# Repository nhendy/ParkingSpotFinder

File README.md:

# ECE477-GarageMonitoringSystem

## Links
- [Initial proposal](https://docs.google.com/document/d/1f3pLotd3W6YBDPHfsqi8Z5CGvJJmyrOUrbO1O-sXBOU/edit)

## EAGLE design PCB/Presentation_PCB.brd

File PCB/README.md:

# Pinout

## MCU to CM3 UART5

| STM Pins      | CM3 Pins   | Functionality   |
| ------------- | ---------- | --------------- |
| PD_2          | 51          | USART5 RX  -->  GPIO14 TX|
| PC_12         | 53          | USART5 TX  -->  GPIO15 RX|
## MCU to JTAG
| STM Pins      | JTAG Pins    | Functionality   |
| ------------- | ----------   | --------------- |
| PA_13         | 1            | SWDIO  -->  VDD|
| PA_14         | 2            | SWCLK  -->  SWDIO|
| PA_15         | 3,5,9        | JTDI  -->  GND|
| PB_3          | 6            | SWO   -->  SWO|
| PB_4          | 10           | JTRST  -->  RST|

## MCU to Sensor UART7
| STM Pins      | Sensor Pins    | Functionality   |
| ------------- | ----------   | --------------- |
| PF_6         | Pin 5            | RX  -->  Serial out|
| PA_7         | _          | |
## MCU to LCD
| STM Pins      | LCD Pins    | Functionality   |
| ------------- | ----------   | --------------- |
| PB_2         | 3            | QUAD_SPI_SCLK  |
| PE_7         | 5            | QUAD_SPI_IO0  |
| PE_8         | 4            | QUAD_SPI_IO1|
| PE_9         | 11           | QUAD_SPI_IO2|
| PE_10         | 12          | QUAD_SPI_IO3|

## MCU to FTDI UART1

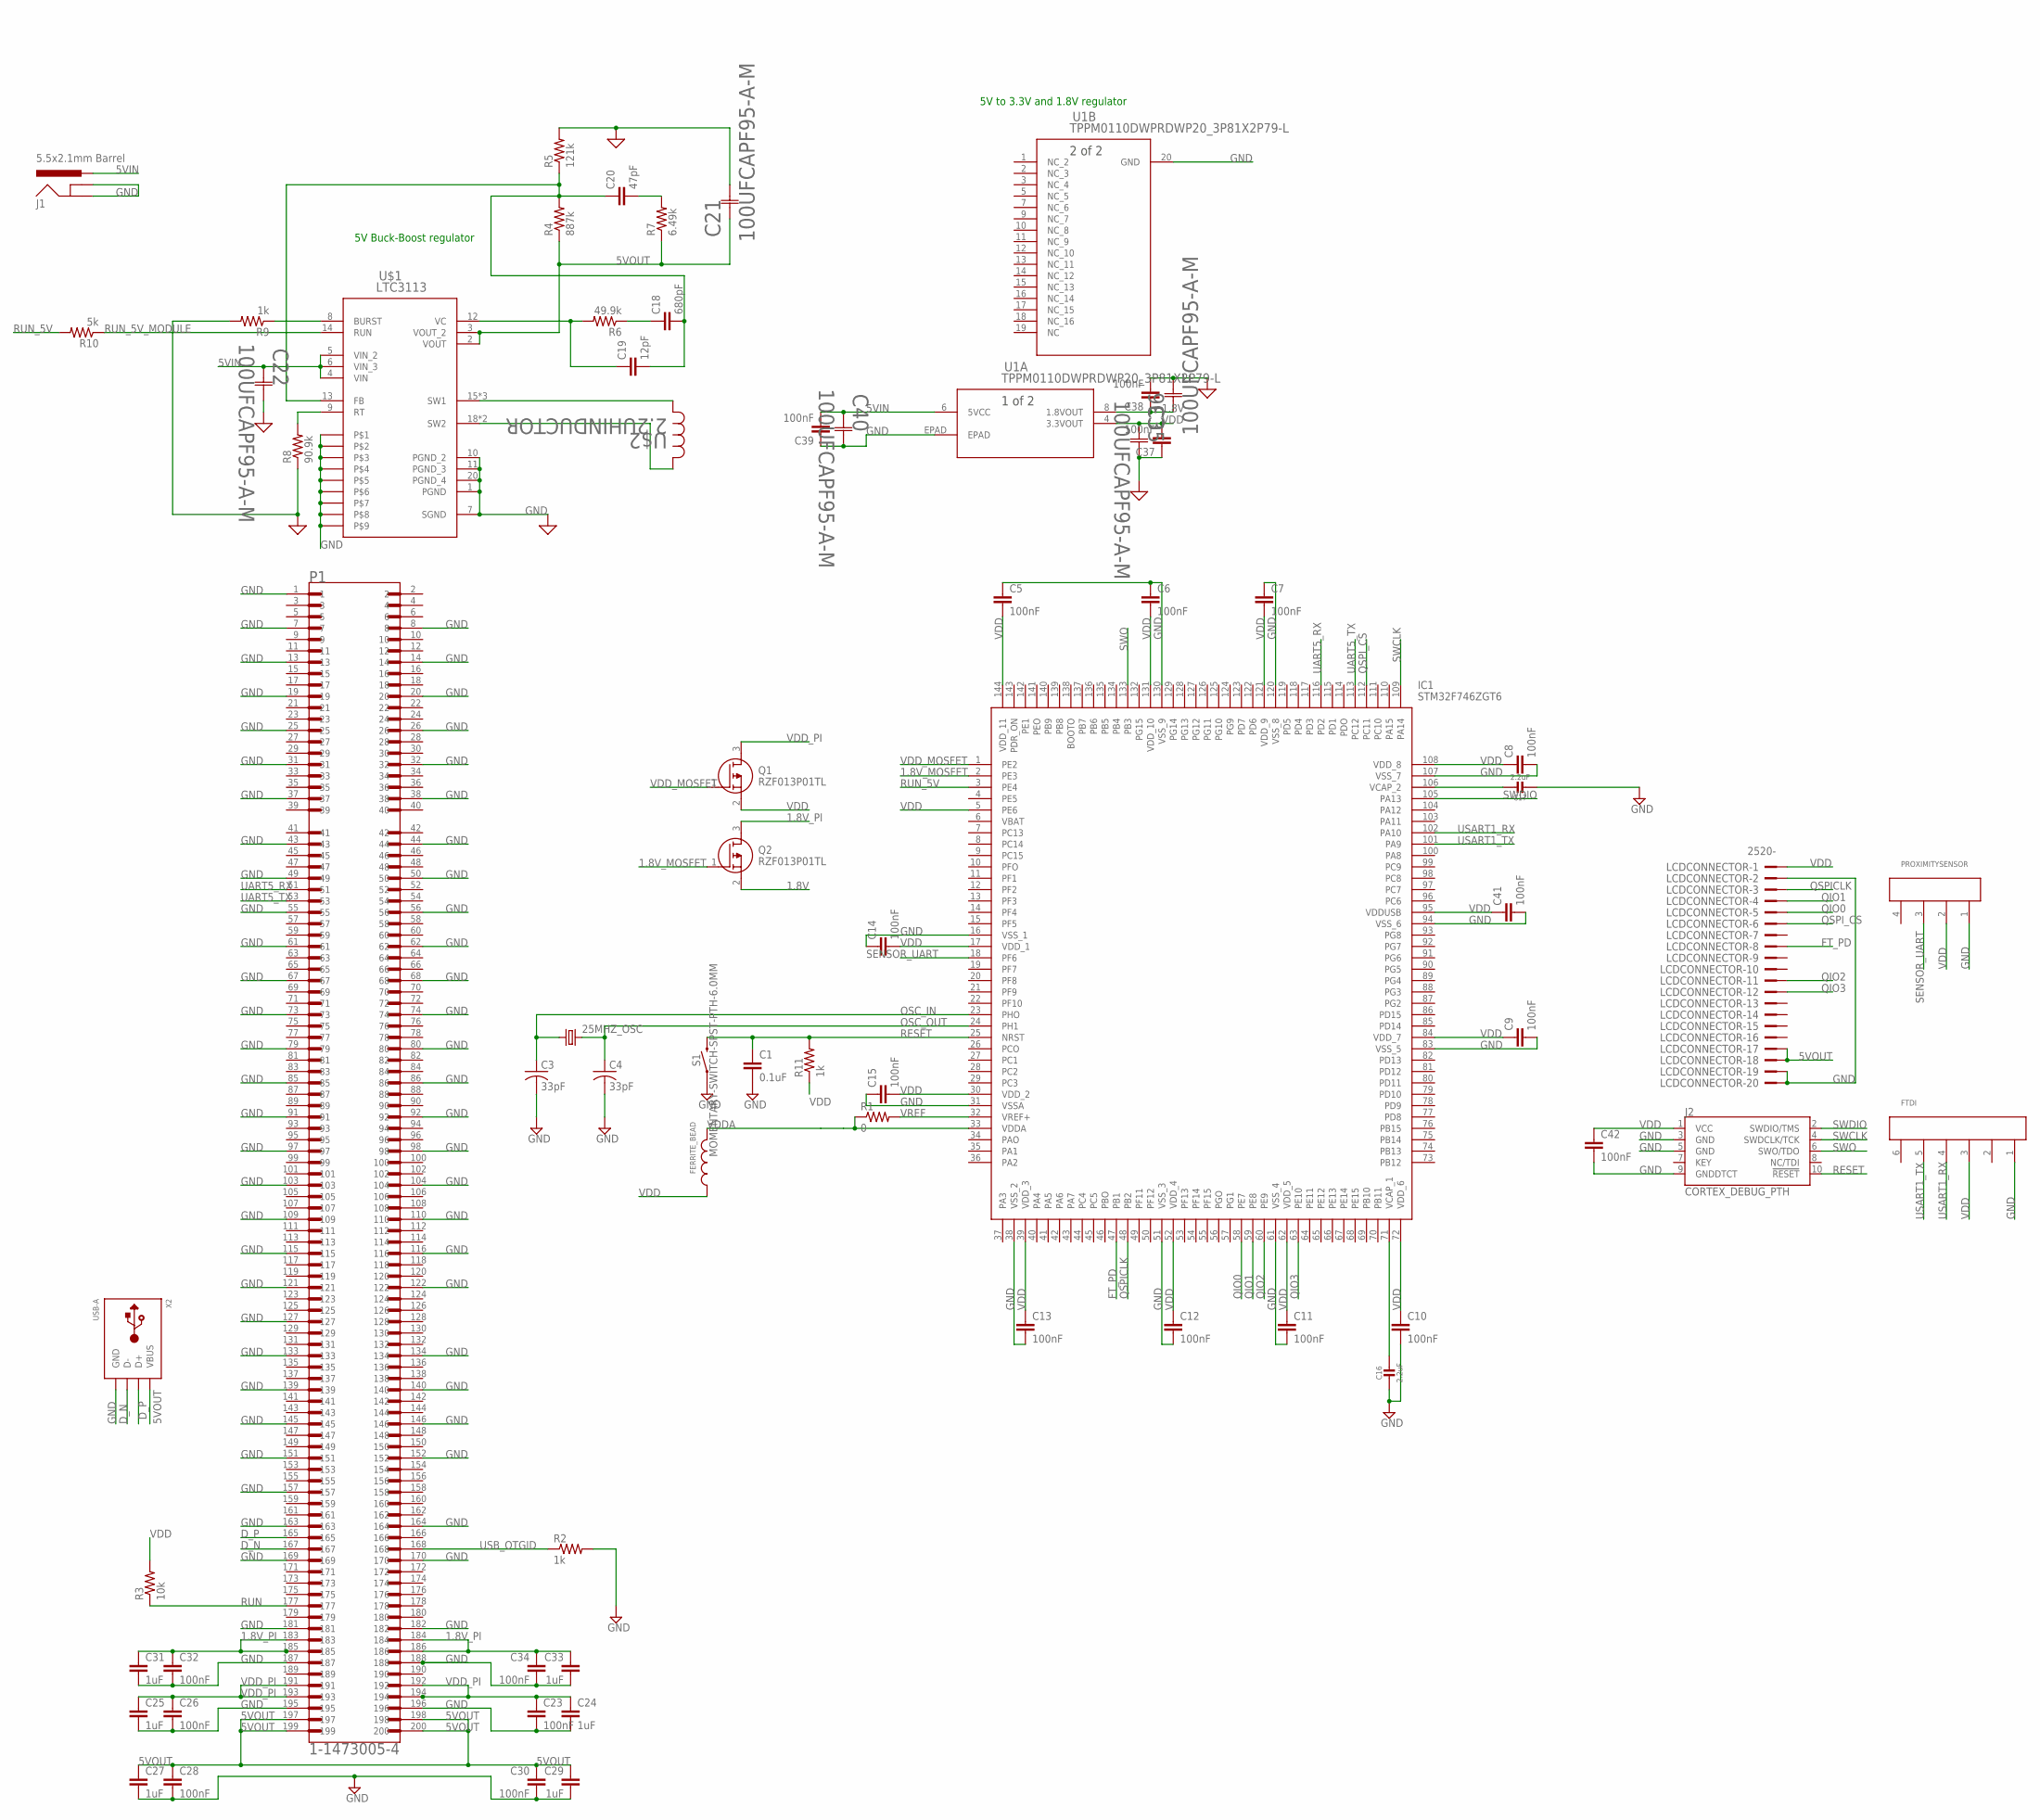
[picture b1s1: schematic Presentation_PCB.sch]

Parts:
25MHZ_OSC: CRYSTALHC49UP; HC49UP
C1: 0.1uF; C0805
C3, C4: 33pF; C0805
C5, C6, C7, C8, C9, C10, C11, C12, C13, C14, C15, C23, C26, C28, C30, C32, C34, C37, C38, C39, C41, C42: 100nF; C0805
C16, C17: 2.2uF; 0805-NO
C18: 680pF; C0805
C19: 12pF; C0805
C20: 47pF; C0805
C21, C22, C35, C36, C40: 100UFCAPF95-A-M; F95-A-M
C24, C25, C27, C29, C31, C33: 1uF; C0805
FERRITE_BEAD: WE-CBA_0805_782853112_HC; WE-CBA_0805(W=4)
FTDI: 66100611622
IC1: STM32F746ZGT6; QFP50P2200X2200X160-144N
J1: 5.5x2.1mm Barrel; POWER_JACK_SMD
J2: CORTEX_DEBUG_PTH; 2X5-PTH-1.27MM
LCDCONNECTOR: 2520-; PAK100/2500-20
P1: 1-1473005-4; TE_1-1473005-4
PROXIMITYSENSOR: 66100411622
Q1, Q2: RZF013P01TL; SOT65P210X85-3N
R1: 0; R0805
R2, R9, R11: 1k; R0805
R3: 10k; R0805
R4: 887k; R0805
R5: 121k; R0805
R6: 49.9k; R0805
R7: 6.49k; R0805
R8: 90.9k; R0805
R10: 5k; R0805
S1: MOMENTARY-SWITCH-SPST-PTH-6.0MM; TACTILE_SWITCH_PTH_6.0MM
U1: TPPM0110DWPRDWP20_3P81X2P79-L; DWP20_3P81X2P79-L
U$1: LTC3113; TSSOP-20_FE/CA
U$2: 2.2UHINDUCTOR; IND_10040
X2: USB-A; MOLEX_480371000

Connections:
1.8V: C36.1, C38.1, Q2.2 (S), U1.8 (1.8VOUT)
1.8V_MOSFET: IC1.2 (PE3), Q2.1 (G)
1.8V_PI: C31.1, C32.1, C33.1, C34.1, P1.183, P1.184, P1.185, P1.186, Q2.3 (D)
5VIN: C22.1, C39.2, C40.1, J1.VIN0 (PWR), U1.6 (5VCC), U$1.4 (VIN), U$1.5 (VIN_2), U$1.6 (VIN_3)
5VOUT: C21.1, C27.1, C28.1, C29.1, C30.1, LCDCONNECTOR.17, LCDCONNECTOR.18, P1.197, P1.198, P1.199, P1.200, R4.1, R7.1, U$1.2 (VOUT), U$1.3 (VOUT_2), X2.1 (VBUS)
D_N: P1.167, X2.2 (D-)
D_P: P1.165, X2.3 (D+)
FT_PD: IC1.47 (PB1), LCDCONNECTOR.8
GND: C1.2, C3.2, C4.2, C5.1, C6.1, C7.1, C8.2, C9.2, C10.2, C11.2, C12.2, C13.2, C14.1, C15.1, C16.2, C17.2, C21.2, C22.2, C23.2, C24.2, C25.2, C26.2, C27.2, C28.2, C29.2, C30.2, C31.2, C32.2, C33.2, C34.2, C35.2, C36.2, C37.1, C38.2, C39.1, C40.2, C41.2, C42.2, FTDI.1, IC1.16 (VSS_1), IC1.31 (VSSA), IC1.38 (VSS_2), IC1.51 (VSS_3), IC1.61 (VSS_4), IC1.83 (VSS_5), IC1.94 (VSS_6), IC1.107 (VSS_7), IC1.120 (VSS_8), IC1.130 (VSS_9), J1.GND (GNDBREAK), J1.P$4 (GND), J2.3 (GND), J2.5 (GND), J2.9 (GNDDTCT), LCDCONNECTOR.2, LCDCONNECTOR.19, LCDCONNECTOR.20, P1.1, P1.7, P1.8, P1.13, P1.14, P1.19, P1.20, P1.25, P1.26, P1.31, P1.32, P1.37, P1.38, P1.43, P1.44, P1.49, P1.50, P1.55, P1.56, P1.61, P1.62, P1.67, P1.68, P1.73, P1.74, P1.79, P1.80, P1.85, P1.86, P1.91, P1.92, P1.97, P1.98, P1.103, P1.104, P1.109, P1.110, P1.115, P1.116, P1.121, P1.122, P1.127, P1.133, P1.134, P1.139, P1.140, P1.145, P1.146, P1.151, P1.152, P1.157, P1.163, P1.164, P1.169, P1.170, P1.181, P1.182, P1.187, P1.188, P1.195, P1.196, PROXIMITYSENSOR.1, R2.2, R5.2, R8.1, R9.2, S1.1, U1.20 (GND), U1.EPAD, U$1.1 (PGND), U$1.7 (SGND), U$1.10 (PGND_2), U$1.11 (PGND_3), U$1.20 (PGND_4), U$1.P$1, U$1.P$2, U$1.P$3, U$1.P$4, U$1.P$5, U$1.P$6, U$1.P$7, U$1.P$8, U$1.P$9, X2.4 (GND)
unnamed: C16.1, IC1.71 (VCAP_1)
unnamed: C17.1, IC1.106 (VCAP_2)
unnamed: C20.2, R7.2
unnamed: C19.1, R6.2, U$1.12 (VC)
unnamed: C18.1, R6.1
unnamed: C18.2, C19.2, C20.1, R4.2, R5.1, U$1.13 (FB)
unnamed: U$1.15 (SW1), U$1.16 (SW1), U$1.17 (SW1), U$2.2
unnamed: U$1.18 (SW2), U$1.19 (SW2), U$2.1
unnamed: R8.2, U$1.9 (RT)
unnamed: R9.1, U$1.8 (BURST)
OSC_IN: 25MHZ_OSC.1, C3.1, IC1.23 (PHO)
OSC_OUT: 25MHZ_OSC.2, C4.1, IC1.24 (PH1)
QIO0: IC1.58 (PE7), LCDCONNECTOR.5
QIO1: IC1.59 (PE8), LCDCONNECTOR.4
QIO2: IC1.60 (PE9), LCDCONNECTOR.11
QIO3: IC1.63 (PE10), LCDCONNECTOR.12
QSPICLK: IC1.48 (PB2), LCDCONNECTOR.3
QSPI_CS: IC1.112 (PC11), LCDCONNECTOR.6
RESET: C1.1, IC1.25 (NRST), J2.10 (!RESET), R11.2, S1.3 (2)
RUN: P1.177, R3.1
RUN_5V: IC1.3 (PE4), R10.2
RUN_5V_MODULE: R10.1, U$1.14 (RUN)
SENSOR_UART: IC1.18 (PF6), PROXIMITYSENSOR.3
SWCLK: IC1.109 (PA14), J2.4 (SWDCLK/TCK)
SWDIO: IC1.105 (PA13), J2.2 (SWDIO/TMS)
SWO: IC1.133 (PB3), J2.6 (SWO/TDO)
UART5_RX: IC1.116 (PD2), P1.51
UART5_TX: IC1.113 (PC12), P1.53
USART1_RX: FTDI.4, IC1.102 (PA10)
USART1_TX: FTDI.5, IC1.101 (PA9)
USB_OTGID: P1.168, R2.1
VDD: C5.2, C6.2, C7.2, C8.1, C9.1, C10.1, C11.1, C12.1, C13.1, C14.2, C15.2, C35.1, C37.2, C41.1, C42.1, FERRITE_BEAD.1, FTDI.3, IC1.5 (PE6), IC1.17 (VDD_1), IC1.30 (VDD_2), IC1.39 (VDD_3), IC1.52 (VDD_4), IC1.62 (VDD_5), IC1.72 (VDD_6), IC1.84 (VDD_7), IC1.95 (VDDUSB), IC1.108 (VDD_8), IC1.121 (VDD_9), IC1.131 (VDD_10), IC1.144 (VDD_11), J2.1 (VCC), LCDCONNECTOR.1, PROXIMITYSENSOR.2, Q1.2 (S), R3.2, R11.1, U1.4 (3.3VOUT)
VDDA: FERRITE_BEAD.2, IC1.33 (VDDA), R1.1
VDD_MOSFET: IC1.1 (PE2), Q1.1 (G)
VDD_PI: C23.1, C24.1, C25.1, C26.1, P1.191, P1.192, P1.193, P1.194, Q1.3 (D)
VREF: IC1.32 (VREF+), R1.2

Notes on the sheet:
5V to 3.3V and 1.8V regulator
5V Buck-Boost regulator

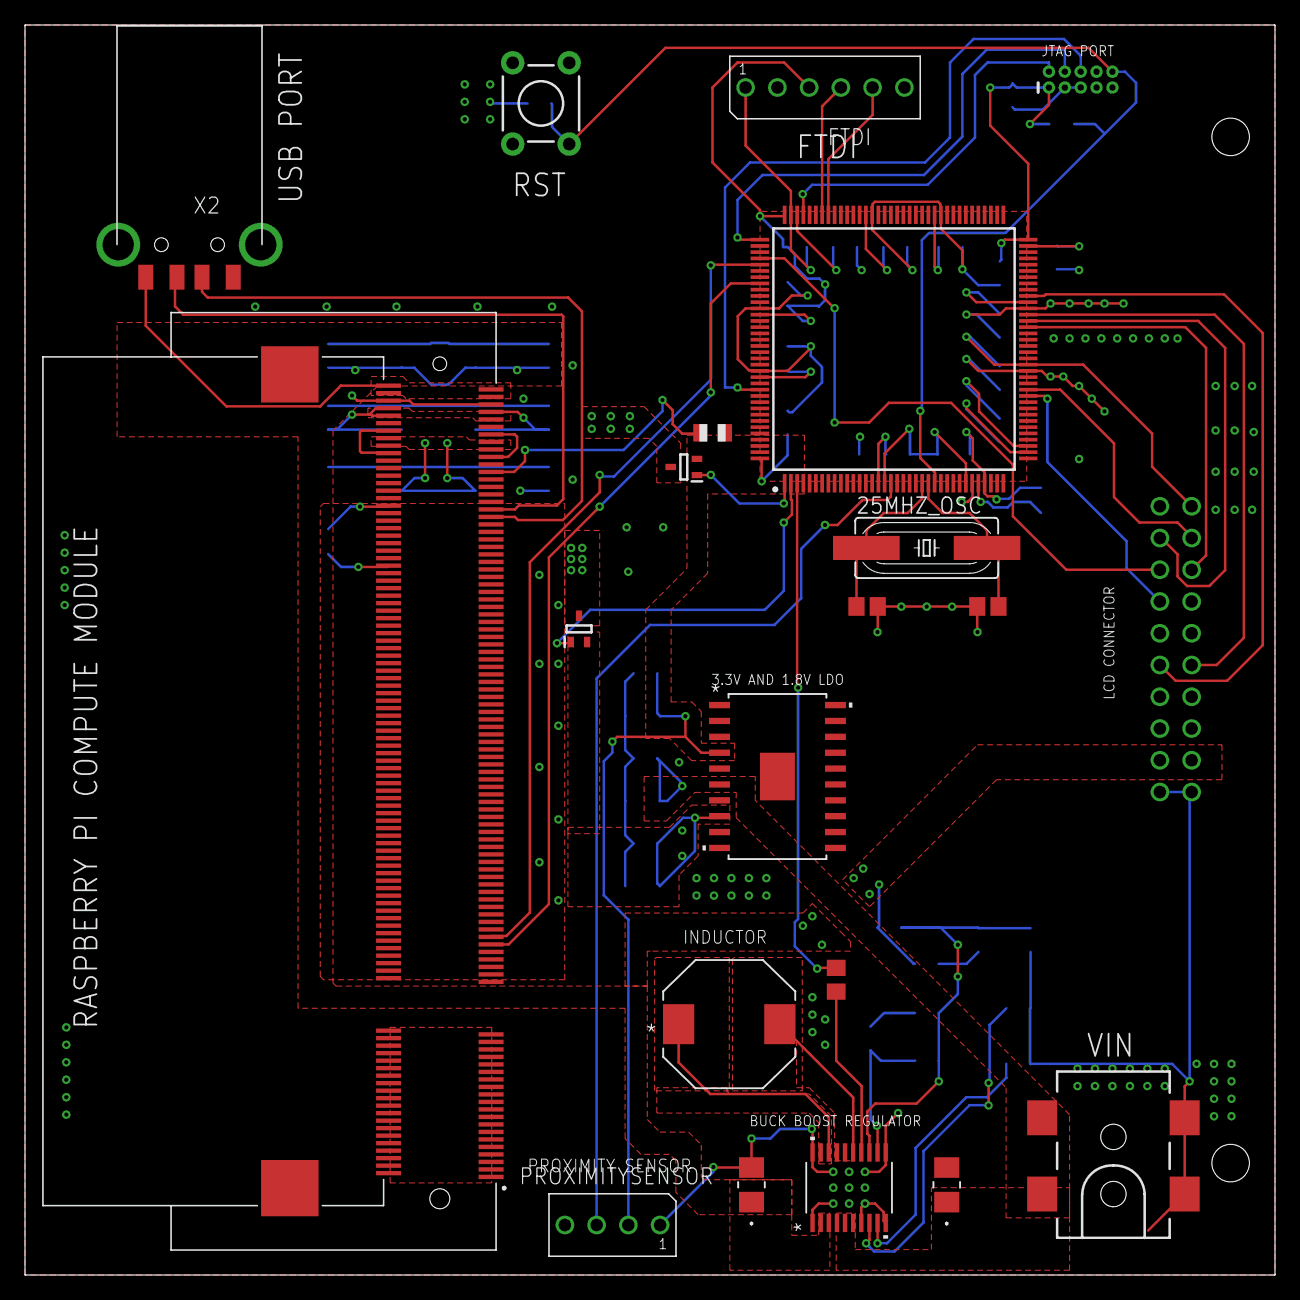
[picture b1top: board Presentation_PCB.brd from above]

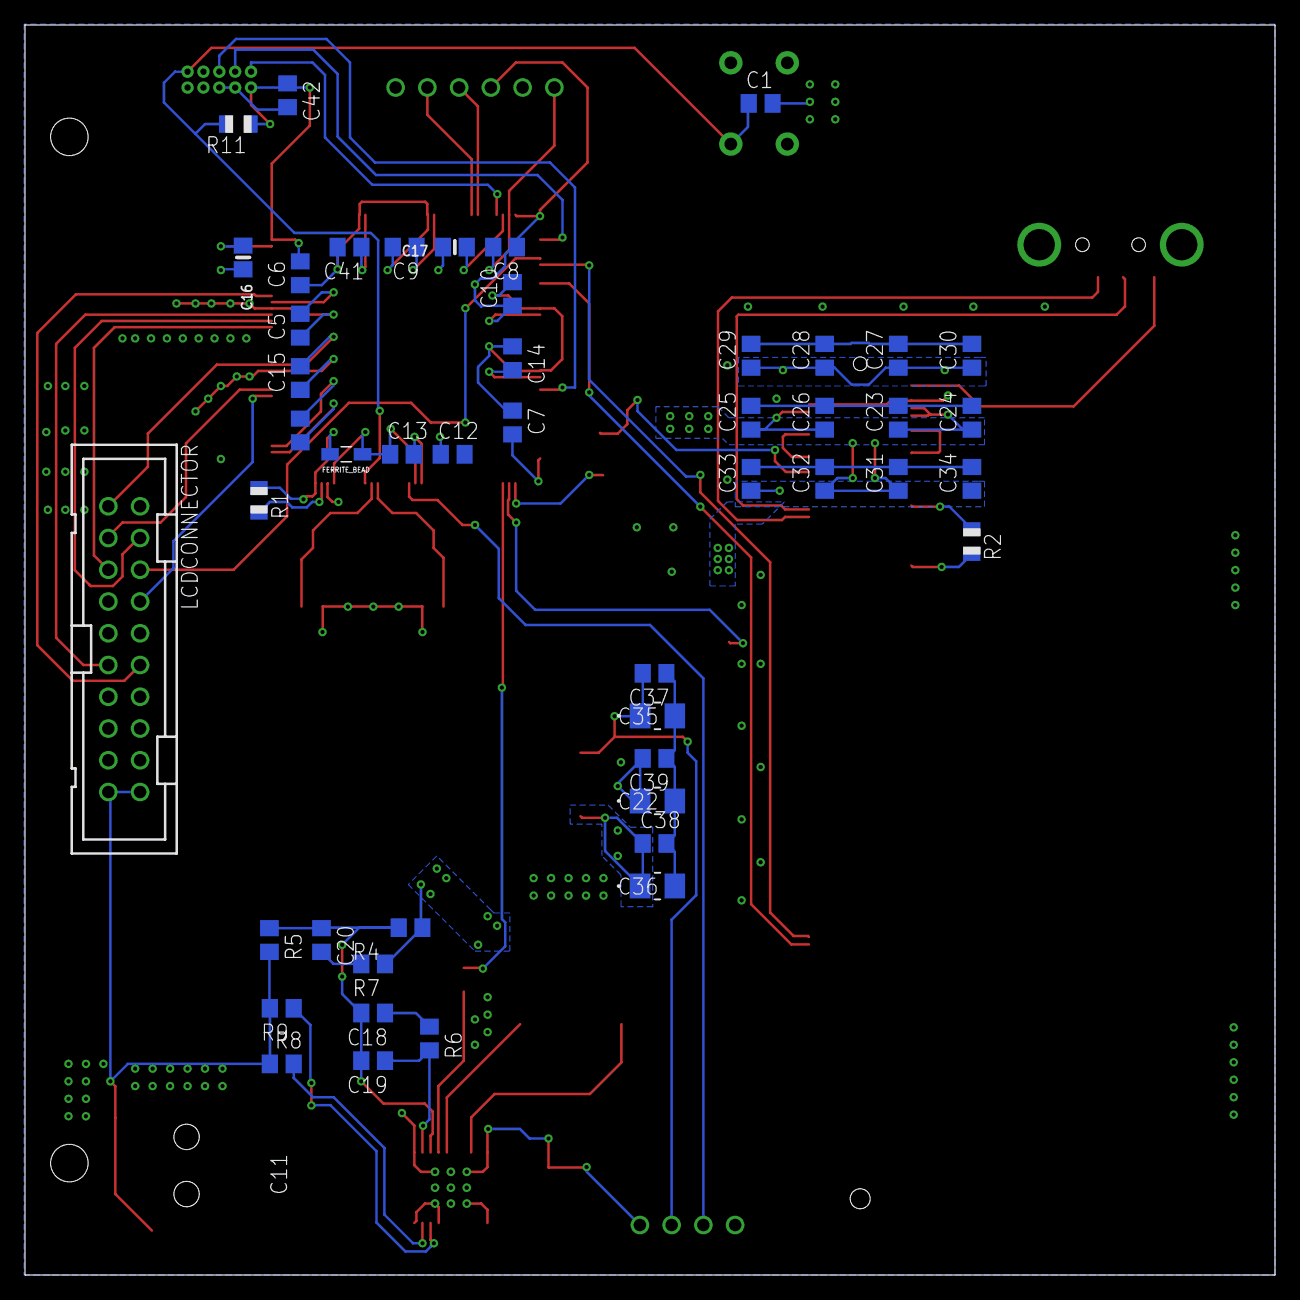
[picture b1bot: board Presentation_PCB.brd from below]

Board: 2 copper layers, 100.0 x 100.0 mm, 69 parts (48 on the bottom side), 45 nets.

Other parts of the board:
DRILEGEND: DRILEGEND

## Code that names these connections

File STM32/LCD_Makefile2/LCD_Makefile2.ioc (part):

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Mcu.Name=STM32F746ZGTx
Mcu.Package=LQFP144
Mcu.UserName=STM32F746ZGTx
PA0/WKUP.Mode=SYS_WakeUp0
PA0/WKUP.Signal=SYS_WKUP1
PA10.GPIOParameters=GPIO_Label
PA10.GPIO_Label=CS
PA10.Signal=GPIO_Output
PA13.Signal=SYS_JTMS-SWDIO
PA14.Signal=SYS_JTCK-SWCLK
PA9.Mode=Asynchronous
PA9.Signal=USART1_TX
PB0.GPIOParameters=GPIO_Label
PB0.GPIO_Label=PD
PB0.Signal=GPIO_Output
PB1.GPIOParameters=GPIO_Label
PB1.GPIO_Label=PD_PCB
PB1.Signal=GPIO_Output
PB11.Mode=Asynchronous
PB11.Signal=USART3_RX
PB2.Mode=Single Bank 2
PB2.Signal=QUADSPI_CLK
PB3.Signal=SYS_JTDO-SWO
PB7.Mode=Asynchronous
PB7.Signal=USART1_RX
PB9.GPIOParameters=GPIO_Label
PB9.GPIO_Label=TEST1
PB9.Signal=GPIO_Output
PC11.GPIOParameters=GPIO_Mode
PC11.GPIO_Mode=GPIO_MODE_AF_PP
PC11.Mode=Single Bank 2
PC11.Signal=QUADSPI_BK2_NCS
PC12.Mode=Asynchronous
PC12.Signal=UART5_TX
PC6.Mode=Asynchronous
PC6.Signal=USART6_TX
PC7.Mode=Asynchronous
PC7.Signal=USART6_RX
PD2.Mode=Asynchronous
PD2.Signal=UART5_RX
PD8.Mode=Asynchronous
PD8.Signal=USART3_TX
PE0.GPIOParameters=GPIO_Label
PE0.GPIO_Label=TEST
PE0.Signal=GPIO_Output
PE1.GPIOParameters=GPIO_Label
PE1.GPIO_Label=PI_RUN
PE1.Signal=GPIO_Input
PE10.Mode=Single Bank 2
PE10.Signal=QUADSPI_BK2_IO3
PE2.GPIOParameters=GPIO_Label
PE2.GPIO_Label=PI_3V3
PE2.Signal=GPIO_Output
PE3.GPIOParameters=GPIO_Label
PE3.GPIO_Label=PI_1V8
PE3.Signal=GPIO_Output
PE4.GPIOParameters=GPIO_Label
PE4.GPIO_Label=PI_5V
PE4.Signal=GPIO_Output
PE7.Mode=Single Bank 2
PE7.Signal=QUADSPI_BK2_IO0
PE8.Mode=Single Bank 2
PE8.Signal=QUADSPI_BK2_IO1
PE9.Mode=Single Bank 2
PE9.Signal=QUADSPI_BK2_IO2
PF6.Mode=Asynchronous
PF6.Signal=UART7_RX
PF7.Mode=Asynchronous
PF7.Signal=UART7_TX
RCC.HSE_VALUE=25000000
RCC.SYSCLKFreq_VALUE=60000000
RCC.SYSCLKSource=RCC_SYSCLKSOURCE_PLLCLK
board=custom

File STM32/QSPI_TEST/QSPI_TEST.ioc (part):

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Mcu.Name=STM32F746ZGTx
Mcu.Package=LQFP144
Mcu.UserName=STM32F746ZGTx
PA1.GPIOParameters=GPIO_Label
PA1.GPIO_Label=RMII_REF_CLK [LAN8742A-CZ-TR_REFCLK0]
PA1.Signal=ETH_REF_CLK
PA10.GPIOParameters=GPIO_Label
PA10.GPIO_Label=USB_ID
PA10.Signal=USB_OTG_FS_ID
PA11.GPIOParameters=GPIO_Label
PA11.GPIO_Label=USB_DM
PA11.Signal=USB_OTG_FS_DM
PA12.GPIOParameters=GPIO_Label
PA12.GPIO_Label=USB_DP
PA12.Signal=USB_OTG_FS_DP
PA13.GPIOParameters=GPIO_Label
PA13.GPIO_Label=TMS
PA13.Mode=Serial_Wire
PA13.Signal=SYS_JTMS-SWDIO
PA14.GPIOParameters=GPIO_Label
PA14.GPIO_Label=TCK
PA14.Mode=Serial_Wire
PA14.Signal=SYS_JTCK-SWCLK
PA2.GPIOParameters=GPIO_Label
PA2.GPIO_Label=RMII_MDIO [LAN8742A-CZ-TR_MDIO]
PA2.Signal=ETH_MDIO
PA5.Mode=Full_Duplex_Master
PA5.Signal=SPI1_SCK
PA6.Mode=Full_Duplex_Master
PA6.Signal=SPI1_MISO
PA7.GPIOParameters=GPIO_Label
PA7.GPIO_Label=RMII_CRS_DV [LAN8742A-CZ-TR_CRS_DV]
PA7.Signal=ETH_CRS_DV
PA8.GPIOParameters=GPIO_Label
PA8.GPIO_Label=USB_SOF [TP1]
PA8.Signal=USB_OTG_FS_SOF
PA9.GPIOParameters=GPIO_Label
PA9.GPIO_Label=USB_VBUS
PA9.Signal=USB_OTG_FS_VBUS
PB0.GPIOParameters=GPIO_Label
PB0.GPIO_Label=LD1 [Green]
PB0.Signal=GPIO_Output
PB13.GPIOParameters=GPIO_Label
PB13.GPIO_Label=RMII_TXD1 [LAN8742A-CZ-TR_TXD1]
PB13.Signal=ETH_TXD1
PB14.GPIOParameters=GPIO_Label
PB14.GPIO_Label=LD3 [Red]
PB14.Signal=GPIO_Output
PB2.Mode=Single Bank 2 2IOs
PB2.Signal=QUADSPI_CLK
PB3.GPIOParameters=GPIO_Label
PB3.GPIO_Label=SW0
PB3.Signal=SYS_JTDO-SWO
PB5.Mode=Full_Duplex_Master
PB5.Signal=SPI1_MOSI
PB7.GPIOParameters=GPIO_Label
PB7.GPIO_Label=LD2 [Blue]
PB7.Signal=GPIO_Output
PC1.GPIOParameters=GPIO_Label
PC1.GPIO_Label=RMII_MDC [LAN8742A-CZ-TR_MDC]
PC1.Signal=ETH_MDC
PC11.Mode=Single Bank 2 2IOs
PC11.Signal=QUADSPI_BK2_NCS
PC13.GPIOParameters=GPIO_Label
PC13.GPIO_Label=USER_Btn [B1]
PC13.Signal=GPXTI13
PC14/OSC32_IN.Mode=LSE-External-Oscillator
PC14/OSC32_IN.Signal=RCC_OSC32_IN
PC15/OSC32_OUT.Mode=LSE-External-Oscillator
PC15/OSC32_OUT.Signal=RCC_OSC32_OUT
PC4.GPIOParameters=GPIO_Label
PC4.GPIO_Label=RMII_RXD0 [LAN8742A-CZ-TR_RXD0]
PC4.Signal=ETH_RXD0
PC5.GPIOParameters=GPIO_Label
PC5.GPIO_Label=RMII_RXD1 [LAN8742A-CZ-TR_RXD1]
PC5.Signal=ETH_RXD1
PC6.Mode=Asynchronous
PC6.Signal=USART6_TX
PC7.Mode=Asynchronous
PC7.Signal=USART6_RX
PD8.GPIOParameters=GPIO_Label
PD8.GPIO_Label=STLK_RX [STM32F103CBT6_PA3]
PD8.Signal=USART3_TX
PD9.GPIOParameters=GPIO_Label
PD9.GPIO_Label=STLK_TX [STM32F103CBT6_PA2]
PD9.Signal=USART3_RX
PE7.Mode=Single Bank 2 2IOs
PE7.Signal=QUADSPI_BK2_IO0
PE8.Mode=Single Bank 2 2IOs
PE8.Signal=QUADSPI_BK2_IO1
PG11.GPIOParameters=GPIO_Label
PG11.GPIO_Label=RMII_TX_EN [LAN8742A-CZ-TR_TXEN]
PG11.Signal=ETH_TX_EN
PG13.GPIOParameters=GPIO_Label
PG13.GPIO_Label=RMII_TXD0 [LAN8742A-CZ-TR_TXD0]
PG13.Signal=ETH_TXD0
PG6.GPIOParameters=GPIO_Label
PG6.GPIO_Label=USB_PowerSwitchOn [STMPS2151STR_EN]
PG6.Signal=GPIO_Output
PG7.GPIOParameters=GPIO_Label
PG7.GPIO_Label=USB_OverCurrent [STMPS2151STR_FAULT]
PG7.Signal=GPIO_Input
PH0/OSC_IN.GPIOParameters=GPIO_Label
PH0/OSC_IN.GPIO_Label=MCO [STM32F103CBT6_PA8]
PH0/OSC_IN.Mode=HSE-External-Clock-Source
PH0/OSC_IN.Signal=RCC_OSC_IN
PH1/OSC_OUT.Mode=HSE-External-Clock-Source
PH1/OSC_OUT.Signal=RCC_OSC_OUT
RCC.HSE_VALUE=8000000
RCC.SYSCLKFreq_VALUE=72000000
RCC.SYSCLKSource=RCC_SYSCLKSOURCE_PLLCLK
RCC.SYSCLKSourceVirtual=RCC_SYSCLKSOURCE_PLLCLK
board=NUCLEO-F746ZG
boardIOC=true

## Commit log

2019-01-30 hashtable
2019-01-30 fix gitignore
2019-01-31 LSH failing
2019-01-31 modify table
2019-01-31 new hash table
2019-01-31 rm tolerance
2019-02-02 gitignore update
2019-02-04 obj detection
2019-02-04 I love git
2019-02-04 docs
2019-02-06 forward pass
2019-02-11 monster
2019-02-12 preprocessing done
2019-02-12 clean
2019-02-12 rename
2019-02-12 readmes
2019-02-13 fix bug
2019-02-13 Training ready to go!
2019-02-15 Nours_blank_timer
2019-02-16 LCD project with makefile
2019-02-17 version 2
2019-02-17 pcbFiles
2019-02-17 my printf
2019-02-17 working lcd
2019-02-17 fix ignore
2019-02-18 SSD finally trained on a smaller dataset
2019-02-20 flash target
2019-02-20 aapp
2019-02-21 PCBv1.3
2019-02-21 EagleAllNite
2019-02-22 TIMER working!!!
2019-02-22 NOT working LCD
2019-02-24 lilboard
2019-02-25 Reso
2019-02-25 app deployed
2019-02-25 rm unnecessary
2019-02-25 pcbsleep
2019-02-26 FinalBoard
2019-03-03 prez
2019-03-03 pcbee
2019-03-05 loadswtich
2019-03-05 app function
2019-03-07 LCDFIXED
2019-03-08 registration with SQLAlchemy
2019-03-08 log in changed to sqlalchemy
2019-03-08 progress
2019-03-09 screen fix
2019-03-09 query-ing fixed
2019-03-13 new GUI
2019-03-22 reiteration of the app
2019-03-22 revert html
2019-03-22 rm sql
2019-03-24 rm old GUI
2019-03-24 Yes/No pages
2019-03-26 detection and controller logic
2019-03-26 archive obsolete
2019-03-27 TEST firmware
2019-03-31 num pad
2019-04-02 rich
2019-04-02 QSPI
2019-04-02 QSPI test
2019-04-03 detection
2019-04-03 guidone
2019-04-05 qspi nbdata changed
2019-04-05 change
2019-04-05 switch CS and PD
2019-04-05 QSPI and GUI functional
2019-04-07 new app code
2019-04-07 holes
2019-04-07 deep learning is now functioning, accuracy is around 80%
2019-04-12 front end
2019-04-15 added check for vacancy count
2019-04-16 model integrated
2019-04-16 rm edge classificiation
2019-04-16 rm globals
2019-04-16 reorganize
2019-04-16 rm stuff
2019-04-16 working model
2019-04-16 controller & driver
2019-04-16 main loop in progress
2019-04-16 model change
2019-04-16 web app polishing
2019-04-17 admin page
2019-04-17 checkpoint
2019-04-17 current app
2019-04-17 login and admin working
2019-04-17 ignore
2019-04-17 requirements
2019-04-17 images
2019-04-17 config
2019-04-18 sensor com
2019-04-19 uart & dma
2019-04-19 debugging uart changed to uart1
2019-04-19 clean up
2019-04-19 update gitignore
2019-04-19 change name
2019-04-19 clean up again
2019-04-19 sensor working on pcb
2019-04-19 todo
2019-04-20 for new videos
2019-04-21 parameterized my_printf
2019-04-21 latest app
2019-04-21 app changes
2019-04-21 controller
2019-04-22 app new code
2019-04-22 please let this be the last time i fix this
2019-04-23 latest app code, all done ready to deply'
2019-04-23 function to update web server
2019-04-23 function to update web server better
2019-04-24 query server
2019-04-25 fixed gui lag
2019-04-25 latenight
2019-04-25 donezoooo
2019-04-26 lastPush
2019-10-21 Bump werkzeug from 0.14.1 to 0.15.3 in /App
    Bumps [werkzeug](https://github.com/pallets/werkzeug) from 0.14.1 to 0.15.3.
    - [Release notes](https://github.com/pallets/werkzeug/releases)
    - [Changelog](https://github.com/pallets/werkzeug/blob/master/CHANGES.rst)
    - [Commits](https://github.com/pallets/werkzeug/compare/0.14.1...0.15.3)
2020-04-30 Bump jquery from 3.3.1 to 3.5.0 in /App/app/static.backup
    Bumps [jquery](https://github.com/jquery/jquery) from 3.3.1 to 3.5.0.
    - [Release notes](https://github.com/jquery/jquery/releases)
    - [Commits](https://github.com/jquery/jquery/compare/3.3.1...3.5.0)
2020-07-16 Bump lodash from 4.17.11 to 4.17.19 in /App/app/static.backup
    Bumps [lodash](https://github.com/lodash/lodash) from 4.17.11 to 4.17.19.
    - [Release notes](https://github.com/lodash/lodash/releases)
    - [Commits](https://github.com/lodash/lodash/compare/4.17.11...4.17.19)
2020-09-04 Bump node-sass from 4.11.0 to 4.14.1 in /App/app/static.backup
    Bumps [node-sass](https://github.com/sass/node-sass) from 4.11.0 to 4.14.1.
    - [Release notes](https://github.com/sass/node-sass/releases)
    - [Changelog](https://github.com/sass/node-sass/blob/master/CHANGELOG.md)
    - [Commits](https://github.com/sass/node-sass/compare/v4.11.0...v4.14.1)
2020-09-04 Bump lodash.mergewith from 4.6.1 to 4.6.2 in /App/app/static.backup
    Bumps [lodash.mergewith](https://github.com/lodash/lodash) from 4.6.1 to 4.6.2.
    - [Release notes](https://github.com/lodash/lodash/releases)
    - [Commits](https://github.com/lodash/lodash/commits)
2020-10-27 Bump cryptography from 2.6.1 to 3.2 in /App
    Bumps [cryptography](https://github.com/pyca/cryptography) from 2.6.1 to 3.2.
    - [Release notes](https://github.com/pyca/cryptography/releases)
    - [Changelog](https://github.com/pyca/cryptography/blob/master/CHANGELOG.rst)
    - [Commits](https://github.com/pyca/cryptography/compare/2.6.1...3.2)
2020-12-11 Bump ini from 1.3.5 to 1.3.7 in /App/app/static.backup
    Bumps [ini](https://github.com/isaacs/ini) from 1.3.5 to 1.3.7.
    - [Release notes](https://github.com/isaacs/ini/releases)
    - [Commits](https://github.com/isaacs/ini/compare/v1.3.5...v1.3.7)
2021-03-20 Bump jinja2 from 2.10 to 2.11.3 in /App
    Bumps [jinja2](https://github.com/pallets/jinja) from 2.10 to 2.11.3.
    - [Release notes](https://github.com/pallets/jinja/releases)
    - [Changelog](https://github.com/pallets/jinja/blob/master/CHANGES.rst)
    - [Commits](https://github.com/pallets/jinja/compare/2.10...2.11.3)
2021-03-30 Bump y18n from 3.2.1 to 3.2.2 in /App/app/static.backup
    Bumps [y18n](https://github.com/yargs/y18n) from 3.2.1 to 3.2.2.
    - [Release notes](https://github.com/yargs/y18n/releases)
    - [Changelog](https://github.com/yargs/y18n/blob/master/CHANGELOG.md)
    - [Commits](https://github.com/yargs/y18n/commits)
2021-05-08 Bump lodash from 4.17.11 to 4.17.21 in /App/app/static.backup
    Bumps [lodash](https://github.com/lodash/lodash) from 4.17.11 to 4.17.21.
    - [Release notes](https://github.com/lodash/lodash/releases)
    - [Commits](https://github.com/lodash/lodash/compare/4.17.11...4.17.21)
2021-05-10 Bump hosted-git-info from 2.7.1 to 2.8.9 in /App/app/static.backup
    Bumps [hosted-git-info](https://github.com/npm/hosted-git-info) from 2.7.1 to 2.8.9.
    - [Release notes](https://github.com/npm/hosted-git-info/releases)
    - [Changelog](https://github.com/npm/hosted-git-info/blob/v2.8.9/CHANGELOG.md)
    - [Commits](https://github.com/npm/hosted-git-info/compare/v2.7.1...v2.8.9)
2021-05-25 Bump browserslist from 4.4.1 to 4.16.6 in /App/app/static.backup
    Bumps [browserslist](https://github.com/browserslist/browserslist) from 4.4.1 to 4.16.6.
    - [Release notes](https://github.com/browserslist/browserslist/releases)
    - [Changelog](https://github.com/browserslist/browserslist/blob/main/CHANGELOG.md)
    - [Commits](https://github.com/browserslist/browserslist/compare/4.4.1...4.16.6)
2021-06-01 Bump urllib3 from 1.24.1 to 1.26.5 in /App
    Bumps [urllib3](https://github.com/urllib3/urllib3) from 1.24.1 to 1.26.5.
    - [Release notes](https://github.com/urllib3/urllib3/releases)
    - [Changelog](https://github.com/urllib3/urllib3/blob/main/CHANGES.rst)
    - [Commits](https://github.com/urllib3/urllib3/compare/1.24.1...1.26.5)
    ---
    updated-dependencies:
2021-06-15 Bump postcss from 7.0.14 to 7.0.36 in /App/app/static.backup
    Bumps [postcss](https://github.com/postcss/postcss) from 7.0.14 to 7.0.36.
    - [Release notes](https://github.com/postcss/postcss/releases)
    - [Changelog](https://github.com/postcss/postcss/blob/main/CHANGELOG.md)
    - [Commits](https://github.com/postcss/postcss/compare/7.0.14...7.0.36)
    ---
    updated-dependencies:
2021-08-04 Bump tar from 2.2.1 to 2.2.2 in /App/app/static.backup
    Bumps [tar](https://github.com/npm/node-tar) from 2.2.1 to 2.2.2.
    - [Release notes](https://github.com/npm/node-tar/releases)
    - [Changelog](https://github.com/npm/node-tar/blob/main/CHANGELOG.md)
    - [Commits](https://github.com/npm/node-tar/compare/v2.2.1...v2.2.2)
    ---
    updated-dependencies:
2021-08-10 Bump path-parse from 1.0.6 to 1.0.7 in /App/app/static.backup
    Bumps [path-parse](https://github.com/jbgutierrez/path-parse) from 1.0.6 to 1.0.7.
    - [Release notes](https://github.com/jbgutierrez/path-parse/releases)
    - [Commits](https://github.com/jbgutierrez/path-parse/commits/v1.0.7)
    ---
    updated-dependencies:
    - dependency-name: path-parse
2021-10-21 Bump babel from 2.6.0 to 2.9.1 in /App
    Bumps [babel](https://github.com/python-babel/babel) from 2.6.0 to 2.9.1.
    - [Release notes](https://github.com/python-babel/babel/releases)
    - [Changelog](https://github.com/python-babel/babel/blob/master/CHANGES)
    - [Commits](https://github.com/python-babel/babel/compare/v2.6.0...v2.9.1)
    ---
    updated-dependencies:
2022-01-13 Bump follow-redirects from 1.7.0 to 1.14.7 in /App/app/static.backup
    Bumps [follow-redirects](https://github.com/follow-redirects/follow-redirects) from 1.7.0 to 1.14.7.
    - [Release notes](https://github.com/follow-redirects/follow-redirects/releases)
    - [Commits](https://github.com/follow-redirects/follow-redirects/compare/v1.7.0...v1.14.7)
    ---
    updated-dependencies:
    - dependency-name: follow-redirects
2022-02-11 Bump ajv from 6.9.1 to 6.12.6 in /App/app/static.backup
    Bumps [ajv](https://github.com/ajv-validator/ajv) from 6.9.1 to 6.12.6.
    - [Release notes](https://github.com/ajv-validator/ajv/releases)
    - [Commits](https://github.com/ajv-validator/ajv/compare/v6.9.1...v6.12.6)
    ---
    updated-dependencies:
    - dependency-name: ajv
2022-02-12 Bump follow-redirects from 1.7.0 to 1.14.8 in /App/app/static.backup
    Bumps [follow-redirects](https://github.com/follow-redirects/follow-redirects) from 1.7.0 to 1.14.8.
    - [Release notes](https://github.com/follow-redirects/follow-redirects/releases)
    - [Commits](https://github.com/follow-redirects/follow-redirects/compare/v1.7.0...v1.14.8)
    ---
    updated-dependencies:
    - dependency-name: follow-redirects
2022-06-27 Bump copy-props from 2.0.4 to 2.0.5 in /App/app/static.backup
    Bumps [copy-props](https://github.com/gulpjs/copy-props) from 2.0.4 to 2.0.5.
    - [Release notes](https://github.com/gulpjs/copy-props/releases)
    - [Changelog](https://github.com/gulpjs/copy-props/blob/master/CHANGELOG.md)
    - [Commits](https://github.com/gulpjs/copy-props/compare/2.0.4...2.0.5)
    ---
    updated-dependencies:
2022-11-22 Bump engine.io and browser-sync in /App/app/static.backup
    Bumps [engine.io](https://github.com/socketio/engine.io) to 6.2.1 and updates ancestor dependency [browser-sync](https://github.com/BrowserSync/browser-sync). These dependencies need to be updated to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
    Updates `engine.io` from 3.2.1 to 6.2.1
    - [Release notes](https://github.com/socketio/engine.io/releases)
    - [Changelog](https://github.com/socketio/engine.io/blob/main/CHANGELOG.md)
    - [Commits](https://github.com/socketio/engine.io/compare/3.2.1...6.2.1)
    Updates `browser-sync` from 2.26.3 to 2.27.10
2022-12-03 Bump decode-uri-component from 0.2.0 to 0.2.2 in /App/app/static.backup
    Bumps [decode-uri-component](https://github.com/SamVerschueren/decode-uri-component) from 0.2.0 to 0.2.2.
    - [Release notes](https://github.com/SamVerschueren/decode-uri-component/releases)
    - [Commits](https://github.com/SamVerschueren/decode-uri-component/compare/v0.2.0...v0.2.2)
    ---
    updated-dependencies:
    - dependency-name: decode-uri-component
2022-12-08 Bump certifi from 2018.11.29 to 2022.12.7 in /App
    Bumps [certifi](https://github.com/certifi/python-certifi) from 2018.11.29 to 2022.12.7.
    - [Release notes](https://github.com/certifi/python-certifi/releases)
    - [Commits](https://github.com/certifi/python-certifi/compare/2018.11.29...2022.12.07)
    ---
    updated-dependencies:
    - dependency-name: certifi

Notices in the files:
parts and their libraries:
Wurth_Elektronik_Passive_rev18f: Copyright: Würth Elektronik
SparkFun-Connectors: Licensing: Creative Commons ShareAlike 4.0 International - https://creativecommons.org/licenses/by-sa/4.0
